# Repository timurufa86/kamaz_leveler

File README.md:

# Kamaz-Leveler

Прошивка системы выравнивания пневмоподвески (ESP32 + FreeRTOS + GitHub OTA).

- Базовая ветка разработки: **`2.x`** (старая линия; новая — `3.0.0`)
- Скетч старой линии: `kamaz_2_0_0_fr_adafruiti_OTA_NM/` (ESP32 classic, плата v2)
- Скетч новой линии: `kamaz_3_3_0_fr_adafruiti_OTA_NM/` (ESP32-S3, плата v3)
- Репозиторий: https://github.com/timurufa86/kamaz_leveler

## Аппаратная часть (PCB)

Проект платы (KiCad 10, 2 слоя, корпус 15-8) лежит в [`hardware/`](hardware/README.md).
Там же — документация, рендеры, производственные файлы и скрипты экспорта.

## Toolchain

- **arduino-cli** 1.5.1+
- Ядро: **esp32:esp32 3.3.11+**
- Библиотеки: из `C:\my\libraries` (подключаются через `arduino-cli.yaml`)

## Сборка

Библиотеки подключаются через проектный `arduino-cli.yaml`, где
`directories.user: C:/my` — то есть sketchbook указывает на `C:\my`, а
библиотеки берутся из `C:\my\libraries`.

```powershell
# Компиляция (экспортирует *.bin в build/esp32.esp32.esp32/)
./build.cmd

# Компиляция + прошивка на подключённую плату
./build.cmd COM5
```

Или напрямую:

```powershell
arduino-cli compile --config-file arduino-cli.yaml `
  -b "esp32:esp32:esp32:PartitionScheme=custom,FlashSize=4M" --warnings none --export-binaries `
  --build-property compiler.c.elf.extra_flags=-Wl,--allow-multiple-definition `
  kamaz_2_0_0_fr_adafruiti_OTA_NM
```

> `--warnings none` обязателен: библиотека GEM 1.8.1 содержит функцию без
> `return`, которую ядро ESP32 превращает в ошибку через `-Werror=return-type`.
> (Значение можно передавать как `-Wl,--allow-multiple-definition` или через
> `-D`, главное — попасть в `compiler.c.elf.extra_flags`.)

> `--build-property compiler.c.elf.extra_flags=-Wl,--allow-multiple-definition`
> обязателен, начиная с 8.6.0: библиотека GEM компилируется целиком (включая
> `GEM_u8g2.cpp`), из-за чего в сборку попадает библиотека `U8g2`, а её
> `src/clib/u8g2_fonts.c` дублирует символы шрифтов из
> `U8g2_for_Adafruit_GFX/src/u8g2_fonts.c`. Флаг разрешает дубликаты: линковщик
> оставляет первое определение, неиспользуемые секции удаляются `--gc-sections`.
> Без флага сборка падает на этапе линковки с `multiple definition of
> 'u8g2_font_...'`.

## Карта флеша (4 МБ, своя таблица разделов)

Плата оснащена **4 МБ** флеш-памяти. Штатные OTA-слоты ядра (1.25 МБ) малы
для скетча (~1.6 МБ), поэтому используется **своя схема разделов**
(`kamaz_2_0_0_fr_adafruiti_OTA_NM/partitions.csv`, `PartitionScheme=custom`):

| Раздел | Смещение | Размер | Назначение |
|---|---|---|---|
| `nvs` | 0x9000 | 20 КБ | Wi-Fi/настройки IDF |
| `otadata` | 0xe000 | 8 КБ | выбор OTA-слота |
| `app0` (ota_0) | 0x10000 | **1.75 МБ** | основной слот прошивки |
| `app1` (ota_1) | 0x1D0000 | **1.75 МБ** | слот для OTA-обновления |
| `spiffs` | 0x390000 | 384 КБ | LittleFS (`/config.txt`) |
| `coredump` | 0x3F0000 | 64 КБ | дамп при сбое |

Скетч ~1.6 МБ занимает ~87% слота; запас роста ~230 КБ на слот.

> ⚠️ **Смена карты флеша требует разовой прошивки по USB** (bootloader +
> partitions + app). OTA с прежней 16-мегабайтной схемы разделы НЕ переносит.

## Карта флеша (16 МБ, своя таблица разделов) — линия 3.0.0

Плата v3 (ESP32-S3) оснащена **16 МБ** флеш-памяти. Штатная схема
`PartitionScheme=default_8MB` содержит **один** слот приложения, поэтому OTA на
ней невозможен. Используется **своя схема разделов**
(`kamaz_3_3_0_fr_adafruiti_OTA_NM/partitions.csv`, `PartitionScheme=custom`):

| Раздел | Смещение | Размер | Назначение |
|---|---|---|---|
| `nvs` | 0x9000 | 20 КБ | Wi-Fi/настройки IDF |
| `otadata` | 0xe000 | 8 КБ | выбор OTA-слота |
| `app0` (ota_0) | 0x10000 | **2 МБ** | основной слот прошивки |
| `app1` (ota_1) | 0x210000 | **2 МБ** | слот для OTA-обновления |
| `spiffs` | 0x410000 | 11.9 МБ | LittleFS (`/config.txt`) |
| `coredump` | 0xFF0000 | 64 КБ | дамп при сбое |

Образ ~1.65 МБ, запас роста ~350 КБ на слот. Сборка:
`build_3_3_0.cmd` (FQBN `esp32:esp32:esp32s3:PartitionScheme=custom,FlashSize=16M,PSRAM=opi`).

> ⚠️ **Смена карты флеша требует разовой прошивки по USB** (bootloader +
> partitions + app). OTA с прежней `default_8MB` схемы разделы НЕ переносит.

## Две линии в одном репозитории (фильтр OTA по MAJOR)

Обе линии публикуют ассеты `kamaz_leveler.bin` / `kamaz_leveler.bin.sha256` в
одном репозитории, поэтому устройство фильтрует релизы по **MAJOR** из своего
`VERSION` (`ota_list.cpp`, `releaseMatchesLocalMajor`): релиз с другим MAJOR или
непарсящимся тегом пропускается с логом
`[OTA] skip release v3.0.0 (major 3 != 2)`. Устройство 2.0.0 никогда не
поставит образ 3.0.0 (ESP32-S3) и наоборот.

## Используемые библиотеки

Резолвятся из `C:\my\libraries`:

| Библиотека | Версия |
|---|---|
| ArduinoJson | 7.4.3 |
| Adafruit BusIO | 1.17.4 |
| Adafruit GFX Library | 1.12.6 |
| Adafruit ST7735 and ST7789 Library | 1.11.0 |
| Adafruit ADS1X15 | 2.6.2 |
| EncButton | 3.7.6 |
| GEM | 1.8.1 |
| GyverFilters | 3.3.0 |
| MPU6050 | 1.4.5 |
| U8g2_for_Adafruit_GFX | 1.8.0 |
| U8g2 (только как источник шрифтов, напрямую не подключается) | 2.36.19 |

## Настройки и сервис (8.8.0)

Новые параметры меню (все сохраняются в `/config.txt`, формат **3**, и подгружаются
при старте; старые `config.txt` форматов 1–2 читаются, новые поля = значения по умолчанию):

| Раздел меню | Пункты | Значение по умолчанию |
|---|---|---|
| Давление | Проверка МП,с | 240 |
| Клапаны | Макс.время,с; Зона нечувств.,бар | 10; 0.20 |
| Авторежим | Грубая зона; Точная зона; Порог «хуже» | 0.40; 0.15; 1.20 |
| Движение | Длительность,с; Успокоение,с; Проверка,с; Допуск,бар; Порог гиро; Порог аксель | 30/30/120/0.2/50/1000 |
| Дисплей | Гасить,мин (0 = никогда); Интервал,мс; Порог углов; Порог давл. | 0; 50; 0.05; 0.03 |
| IMU / MPU6050 | Порог детектора; Нуль X,град; Нуль Y,град | 100; 0.0; 0.0 |

Запись конфига — атомарная (`config.tmp` → `config.txt`, предыдущая версия в
`config.bak`), после записи файл проверяется чтением; при старте и после
сохранения в Serial печатается дамп всех значений (`[CFG] …`). Страница меню
**«Настройки»** показывает текущие значения на экране.

### Новые разделы меню

- **«IMU / MPU6050»**
  - **Обнулить углы** — текущее положение становится нулём (с подтверждением
    КН3/КН4); нуль сохраняется в конфиг и учитывается в показаниях и в авторежиме.
  - **Калибровка офсетов** — библиотечная `CalibrateGyro`/`CalibrateAccel` (DMP на
    время калибровки выключается), 6 офсетов сохраняются в конфиг и применяются при
    старте. Требуется ровная площадка и неподвижная машина 10–20 с.
  - **Диагностика MPU** — DeviceID, температура, углы, сырые `getMotion6`, офсеты,
    признак ошибки MPU.
  - **Порог детектора** — аппаратный `setMotionDetectionThreshold` (20…255).
- **Ручной тест клапанов** (раздел «Тестирование») — 6 выходов: ПЛ, ПП, ЗЛ, ЗП,
  НАКАЧКА, СБРОС. Кн1/Кн2 — выбор, **клапан открыт, пока удерживается КН3**,
  Кн4 — выход с закрытием всех клапанов; страховочный таймаут 15 с; доступно
  только в РУЧНОМ режиме без ошибок и вне OTA; аварийная остановка КН4+КН5
  также закрывает клапаны.
- **Гашение подсветки** — по бездействию N минут (`Дисплей → Гасить,мин`);
  первое нажатие только включает подсветку и не выполняет действие.

## Визуализация: экран ДВИЖЕНИЯ (8.9.0)

В режиме ДВИЖЕНИЯ главный экран автоматически сменяется отдельным «экраном движения»:

- цели передних/задних подушек (из настроек) vs текущие давления и рассогласование Δ
  с цветом по допуску (`Движение → Допуск,бар`);
- четыре карточки подушек: текущее значение, метка цели на полосе, Δ по каждой подушке;
- таймеры: «в движении N с», «СТАБИЛИЗАЦИЯ N с» (полоса), «след. проверка N с»,
  «последняя подкачка N с назад»;
- активные клапаны (накачка/сброс передних/задних) с анимацией «бегущих штрихов»;
- тренд (спарклайн) давлений за 30 с: две линии (перед/зад) + штриховые линии целей;
- режимные иконки из `icon.h` в статус-баре (20×20) и пульсирующий бейдж движения в шапке;
- сглаживание (интерполяция) значений и частичная перерисовка — без мерцания.

Логика движения и выравнивания не менялась — экран только читает данные. Наружу вынесены
две переменные времени последней корректировки (`movementLastAdjustFront/Rear`) и
добавлена отметка начала движения (`movementStartMs`).

## Меню и обновления (8.7.0)

- **Вход в меню** — удержание пары **КН3 + КН4** (GPIO15 + GPIO17, 2 с) из любого
  режима и экрана. **Аварийный стоп** — удержание пары **КН1 + КН4**
  (GPIO13 + GPIO17, 2 с); он обрабатывается первым и подавляет открытие меню.
- В меню: Кн1/Кн2 — навигация, Кн3 — ОК, Кн4 — назад (пункт «Назад» создаёт GEM для
  подстраниц), Кн5 — сохранить и выйти. Подсказка дублируется в шапке меню.
- Раздел **«Обновления»**: проверка GitHub, список до 3 релизов
  (`/releases?per_page=3`), карточка релиза (дата, размер, статус, SHA-256),
  установка последней или выбранной версии, режим ArduinoOTA (Wi-Fi).
- Экран прогресса обновления показывается в любом режиме, шапка «ОБНОВЛЕНИЕ»,
  крупный процент и предупреждение «Не выключайте питание».
- Wi-Fi: пароль единый (`asd12345`), экран выбора сети переведён на U8g2 (шкала
  уровня сигнала, усечение длинных имён).
- Страница «Информация» в меню — живая: версия, режим, MPU, давление в магистрали,
  Wi-Fi (SSID/RSSI), аптайм и свободная RAM, число активных ошибок.

## Home Assistant (10.16.0)

Интеграция по **HTTP REST**, включается в меню **Система → Дом (HA)**. Брокер не
нужен: устройство поднимает сервер на порту 80.

- `GET /api/state` — вся телеметрия; `GET /api/config` — все настройки;
  `POST /api/config` — безопасное подмножество; `POST /api/mode` — АВТО/РУЧНОЙ;
  `POST /api/manual` — start/stop/pulse; `POST /api/action` — reset/save/stop/restart.
- Необязательный токен `X-Api-Key` (Serial: `HA TOKEN <стр>`).
- Готовые файлы: `ha/kamaz_leveler_package.yaml`, `ha/kamaz_leveler_dashboard.yaml`,
  инструкция — `docs/HA_INTEGRATION.md`.
- На время OTA сервер останавливается (освобождает сокеты/кучу) и поднимается после.

## Версионирование и релиз

- SemVer: см. `.cursor/rules/semantic-versioning.mdc` (стиль папок/веток `9.0.0`).
- OTA-релиз: см. `.cursor/rules/github-ota-release.mdc`
  (ассеты `kamaz_leveler.bin` + `kamaz_leveler.bin.sha256`, тег `v9.0.0`).

## Типографика и визуализация (появились в 8.6.0)

Весь текст на экранах выводится через **U8g2_for_Adafruit_GFX** (UTF-8, честные
размеры шрифтов, кириллица) — слой из трёх модулей:

| Модуль | Назначение |
|---|---|
| `ui_theme.h` | палитра RGB565, сетка и метрики экрана (отступы, радиусы, высоты строк) |
| `ui_fonts.h` | шрифтовая лестница `UiFont` (Tiny…Huge) — кириллические шрифты U8g2 |
| `ui_text.h` / `.cpp` | класс `UiText` (экземпляр `ui`): печать по базовой линии, выравнивание и вертикальное центрирование в прямоугольнике, `printf`-варианты без динамической памяти, усечение строк с `..` |

Шрифтовая сетка (все с кириллицей):

| Роль | Шрифт | Применение |
|---|---|---|
| Tiny | `u8g2_font_5x7_t_cyrillic` | подсказки, подписи шкал |
| Small | `u8g2_font_6x13_t_cyrillic` | основной мелкий текст, списки |
| SmallB | `u8g2_font_6x13B_t_cyrillic` | акценты и подписи карточек |
| Body / BodyWide | `u8g2_font_7x13` / `8x13_t_cyrillic` | основной текст |
| Med | `u8g2_font_10x20_t_cyrillic` | заголовки экранов, значения |
| Large / XLarge / Huge | `u8g2_font_inr24/33/46_t_cyrillic` | крупные значения, сплэш |

Важно: `U8g2_for_Adafruit_GFX` **не масштабирует** текст (аналога `setTextSize`
нет), поэтому размер задаётся выбором шрифта — глифы остаются пиксель-в-пиксель
вместо растягивания. Меню GEM (`GEM_adafruit_gfx`) по-прежнему работает на
Adafruit-GFX-шрифтах `CourierCyr7`/`CourierCyr9` из `FontsRus/` — только для
пунктов меню; все остальные экраны переведены на U8g2.

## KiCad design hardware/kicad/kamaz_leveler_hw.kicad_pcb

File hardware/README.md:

# Kamaz Leveler — аппаратная часть (PCB)

Плата контроллера пневмоподвески Kamaz Leveler: **ESP32-C3**, 2 слоя, детали с двух сторон.
Проект KiCad 10.0.7. Механика согласована с корпусом **15-8** (чертёж `k_15-08-...pdf`).

## Текущий статус

| Параметр | Значение |
|---|---|
| Схема | `kicad/kamaz_leveler_hw.kicad_sch` — 113 компонентов (U7 = ESP32-C3-DevKitC-02) |
| Плата | `kicad/kamaz_leveler_hw.kicad_pcb` — 83 × 58 мм, 2 слоя, 117 футпринтов |
| Корпус | 4×Ø2,2 NPTH по контуру **28 × 61,6**; модуль сдвинут на −5 мм; J1/J2 — низ (окно 62×28), J3…J8 — верх (окно 42×20) |
| Разводка | **275 из 284 цепей (96,8%)**, 2394 трассы/вии |
| Электрика DRC | **0 замыканий, 0 нарушений зазора** (правило 0,127 мм) |
| Не разведено | 9 цепей: `/BUT1`, `/VIN_FUSED`, `/VLV_IN2,3,5`, `/ST_U3_34`, `/PRES_IN`, `/VLV_DRV1`, `/VLV_DRV4` |
| Прочие DRC | `copper_edge_clearance` 19, `track_width` 4, `via_dangling` 15, silk ~215, courtyard под модулем (намеренно) |
| Производство | `production/` — Gerber, Excellon, pos.csv, STEP, PDF, BOM (перегенерируется скриптом) |

> **Статус: не финальный релиз.** До производства осталось закрыть 9 цепей и почистить `copper_edge`/`via_dangling`.

## Структура

```
hardware/
├── README.md            ← этот файл
├── HANDOFF.md           ← журнал работ (история решений и бэкапов)
├── AGENT_HANDOFF.md     ← передача контекста следующему агенту (правила, грабли, план)
├── kicad/               ← сам проект KiCad
│   ├── kamaz_leveler_hw.kicad_pro / .sch / .pcb / .prl
│   ├── kamaz_leveler_hw.kicad_dru   ← кастомные правила DRC
│   ├── BOM.csv
│   ├── fp-lib-table, sym-lib-table  ← локальные библиотеки (${KIPRJMOD})
│   ├── kamaz.pretty/, kamaz_leveler_hw.pretty/
│   ├── kamaz_leveler.kicad_sym
│   └── 3dmodels/        ← STEP-модели компонентов
├── docs/                ← HARDWARE.md, CALCULATIONS.md, ТЗ, таблица расстановки
├── images/              ← актуальные рендеры платы и схемы
├── production/          ← выходные файлы для завода (Gerber/сверловка/pos/STEP/PDF/BOM)
├── scripts/             ← экспорт и рендер (см. ниже)
├── 3d/                  ← сборка платы в STEP
└── backups/             ← ключевые бэкапы платы (даты в имени)
```

## Как открыть

1. KiCad 10.0.7 → **File → Open Project** → `kicad/kamaz_leveler_hw.kicad_pro`.
2. Библиотеки подключаются автоматически: `${KIPRJMOD}` указывает на `kicad/`, таблицы `fp-lib-table`/`sym-lib-table` уже в проекте.
3. DRC: `Inspect → Design Rules Checker` (правила — `kamaz_leveler_hw.kicad_dru`).

## Как перегенерировать производство

```bash
"C:\Program Files\KiCad\10.0\bin\python.exe" scripts\export_prod.py
```

Скрипт кладёт в `production/`: Gerber (2 слоя, без Protel-расширений), Excellon + карты сверловки, `pos.csv`, `board.step`, `board.pdf`, `board_stats.txt`, `schematic.pdf`, `BOM.csv`.

## Зависимости

| Что | Где |
|---|---|
| KiCad 10.0.7 (`kicad-cli`, `pcbnew` Python) | `C:\Program Files\KiCad\10.0\` |
| Python с `pcbnew` | `C:\Program Files\KiCad\10.0\bin\python.exe` |
| FreeRouting 2.5.0 + JRE 25 | `C:\my\freerouting\` |
| PIL (для рендеров) | системный Python |

## Известные ограничения / waivers

- **Courtyard под модулем ESP32** — детали на обратной стороне под модулем (высота ≤5 мм) стоят намеренно; DRC это помечает.
- **Silk** — пересечения шелкографии с падами/друг другом: косметика, на электрику не влияет.
- **9 несоединённых цепей** — список выше; для 2 слоёв это остаток после автотрассировки, требует ручной доработки.

## История

- 2026-11-01: перепроектирование под корпус 15-8, новая расстановка (SA по HPWL с весами «трудных» цепей), 275/284.
- 2026-11-04: проект перенесён в этот репозиторий (`hardware/`), структура упорядочена, производство перегенерировано.

Подробный журнал — `HANDOFF.md`.

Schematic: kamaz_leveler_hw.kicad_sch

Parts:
C1, C3, C10, C16, C17, C20, C22, C23, C24, C25, C26, C27, C29, C31, C32, C33, C35: 100nF; C_0805_2012Metric
C2: 470uF; CP_Elec_8x10
C4, C5, C7, C11, C12, C14, C15, C21, C30: 10uF; C_1206_3216Metric
C6: 100uF; CP_EIA-7132-20_AVX-U
C8: 4.7nF; C_0805_2012Metric
C9: 47pF; C_0805_2012Metric
C13: 100uF; CP_EIA-6032-15_Kemet-U_Pad2.25x2.35mm_HandSolder
C18: 10uF; CP_EIA-3528-12_Kemet-T_HandSolder
C19: 10uF; C_0805_2012Metric
C28: 330uF/35V; CP_Elec_8x10
D1: 1.5KE36CA; D_DO-201AD_P15.24mm_Horizontal_Pad2.0_Drill1.3
D2: SS54; D_SMC
D3: SS34; D_SMC
D4, D11, D12, D13, D14, D15, D16: LED; LED_0805_2012Metric
D5, D6, D7, D8, D9, D10: SS34; D_SMA
D17, D18: BZX84C3V3; SOT-23
D20: SMAJ12A; D_SMA
F1: 5A; Fuseholder_Blade_Mini_Keystone_3568
H1, H2, H3, H4: MountingHole_3.2mm_M3_Pad6
J1, J8: Conn_01x02_Pin; PinHeader_1x02_P2.54mm_Vertical
J2: Conn_01x07_Pin; PinHeader_1x07_P2.54mm_Vertical
J3: Conn_01x06_Pin; PinHeader_1x06_P2.54mm_Vertical
J4, J6, J7: Conn_01x04_Pin; PinHeader_1x04_P2.54mm_Vertical
J5: Conn_01x08_Pin; PinHeader_1x08_P2.54mm_Vertical
JP1: Jumper; SolderJumper-2_P1.3mm_Open_RoundedPad1.0x1.5mm
L2: 33uH; L_Bourns_SRP1245A
L3: 10uH; L_Bourns-SRN1060
L4: 10uH; L_Bourns_SRP1245A
Q1: IRF9540N; TO-220-3_Vertical
R1, R4, R9, R11, R12, R13, R14, R15, R16, R18, R19, R29, R30, R31, R32, R33, R34, R35, R36, R37, R38, R39, R42, R43: 10k; R_0805_2012Metric
R2: 47k; R_0805_2012Metric
R3, R41: 100k; R_0805_2012Metric
R5: 6.49k; R_0805_2012Metric
R6: 91k; R_0805_2012Metric
R10: 52.3k; R_0805_2012Metric
R20, R21, R23, R24, R25, R26, R27, R28: 4.7k; R_0805_2012Metric
R22: 1k; R_0805_2012Metric
R40: 20k; R_0805_2012Metric
U1: TPS54560BDDA; SOIC-8-1EP_3.9x4.9mm_P1.27mm_EP2.95x4.9mm_Mask2.71x3.4mm_Th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
U2: AP3211K; SOT-23-6
U3, U4: BTS724G; Infineon_SOIC-20W_7.6x12.8mm_P1.27mm
U5: 74HCT541; SOIC-20W_7.5x12.8mm_P1.27mm
U6: PCAL9555APW; TSSOP-24_4.4x7.8mm_P0.65mm
U7: ESP32-DevKitC_30P; ESP32-C3-DevKitC-02
U8: AMS1117-3.3; SOT-223-3_TabPin2
U11: 78L08; SOT-89-3
U12: 74LVC1G14; SOT-23-5

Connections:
+3V3: C15.1, C17.1, C18.1, C21.1, C22.1, C29.1, C35.1, J4.1, J5.2, J6.1, R18.1, R19.1, R20.1, R21.1, R29.1, R30.1, R31.1, R32.1, R33.1, R34.1, R35.1, R36.1, R37.1, R38.1, R41.1, R43.2, U6.24 (VDD), U8.2 (VO), U12.5 (VCC)
+3V3_ESP: U7.30 (3V3)
+5V: C13.1, C14.1, C16.1, C19.1, C20.1, L3.2, R10.1, R22.1, U5.20 (VCC), U7.15 (VIN), U8.3 (VI)
+12V: C6.1, C7.1, C11.1, C12.1, C30.1, D5.1 (K), D6.1 (K), D7.1 (K), D8.1 (K), D9.1 (K), D10.1 (K), L2.2, R6.1, U2.4 (EN), U2.5 (IN), U3.1 (VBB), U3.10 (VBB), U3.11 (VBB), U3.12 (VBB), U3.15 (VBB), U3.16 (VBB), U3.19 (VBB), U3.20 (VBB), U4.1 (VBB), U4.10 (VBB), U4.11 (VBB), U4.12 (VBB), U4.15 (VBB), U4.16 (VBB), U4.19 (VBB), U4.20 (VBB), U11.3 (IN)
+24V: C1.1, C2.1, C4.1, C5.1, C28.1, D1.1 (A1), Q1.3 (S), R2.1, U1.2 (VIN), U1.3 (EN)
/+8V_SENS: C31.1, J7.1, JP1.1 (A), U11.1 (OUT)
/+24V_IN: F1.1, J1.1
/BOOT1: C3.1, U1.1 (BOOT)
/BOOT2: C10.1, U2.1 (BS)
/BUT1: C23.1, J3.2, R29.2, U6.15 (IO1_2)
/BUT2: C24.1, J3.3, R30.2, U6.16 (IO1_3)
/BUT3: C25.1, J3.4, R31.2, U6.17 (IO1_4)
/BUT4: C26.1, J3.5, R32.2, U6.18 (IO1_5)
/BUT5: C27.1, J3.6, R19.2, U6.19 (IO1_6)
/COMP1: C9.2, R4.1, U1.6 (COMP)
/COMP1_R: C8.1, R4.2
/DISP_BL: J5.8, U7.26 (IO4)
/DISP_CS: J5.7, R18.2, U7.23 (IO5)
/DISP_DC: J5.6, U7.25 (IO16)
/DISP_MOSI: J5.4, U7.16 (IO23)
/DISP_RES: J5.5, U7.21 (IO19)
/DISP_SCLK: J5.3, U7.22 (IO18)
/EXT_8V: J7.4, JP1.2 (B)
/FB1: C9.1, R5.1, R6.2, U1.5 (FB)
/FB2: R9.1, R10.2, U2.3 (FB)
/I2C_SCL: J4.3, J6.3, R21.2, U6.22 (SCL), U7.17 (IO22)
/I2C_SDA: J4.2, J6.2, R20.2, U6.23 (SDA), U7.20 (IO21)
/INT_MCU: R37.2, U6.1 (~INT), U7.7 (IO33)
/LED_A: D4.2 (A), R22.2
/PRES_IN: J8.1, R42.1
/PRES_SW: C33.1, D18.1 (K), R41.2, R42.2, U7.8 (IO25)
/Q1_GATE: Q1.1 (G), R1.1, R2.2
/RT1: R3.1, U1.4 (RT/CLK)
/SPEED_PULSE: U7.5 (IO35), U12.4
/SPEED_SIG: D20.1 (A1), J7.3, R39.1
/SP_DIV: C32.1, D17.1 (K), R39.2, R40.1, U12.2
/ST_U3_12: R33.2, U3.4 (ST1/2), U6.10 (IO0_6)
/ST_U3_34: R34.2, U3.8 (ST3/4), U6.11 (IO0_7)
/ST_U4_12: R35.2, U4.4 (ST1/2), U6.13 (IO1_0)
/ST_U4_34: R36.2, U4.8 (ST3/4), U6.14 (IO1_1)
/SW1: C3.2, D2.1 (K), L2.1, U1.8 (SW)
/SW2: C10.2, D3.1 (K), L3.1, U2.6 (SW)
/VALVE_BUB1: D5.2 (A), D11.2 (A), J2.2, U3.18 (OUT1)
/VALVE_BUB2: D6.2 (A), D12.2 (A), J2.3, U3.17 (OUT2)
/VALVE_BUB3: D7.2 (A), D13.2 (A), J2.4, U3.14 (OUT3)
/VALVE_BUB4: D8.2 (A), D14.2 (A), J2.5, U3.13 (OUT4)
/VALVE_DEFL: D10.2 (A), D16.2 (A), J2.7, U4.17 (OUT2)
/VALVE_INFL: D9.2 (A), D15.2 (A), J2.6, U4.18 (OUT1)
/VIN_FILT: L4.2, Q1.2 (D)
/VIN_FUSED: F1.2, L4.1
/VLV_DRV1: R11.1, U3.3 (IN1), U5.18 (Y0)
/VLV_DRV2: R12.1, U3.5 (IN2), U5.17 (Y1)
/VLV_DRV3: R13.1, U3.7 (IN3), U5.16 (Y2)
/VLV_DRV4: R14.1, U3.9 (IN4), U5.15 (Y3)
/VLV_DRV5: R15.1, U4.3 (IN1), U5.14 (Y4)
/VLV_DRV6: R16.1, U4.5 (IN2), U5.13 (Y5)
/VLV_EN: R38.2, U5.1 (G1), U5.19 (G2), U7.6 (IO32)
/VLV_IN1: U5.2 (A0), U6.4 (IO0_0)
/VLV_IN2: U5.3 (A1), U6.5 (IO0_1)
/VLV_IN3: U5.4 (A2), U6.6 (IO0_2)
/VLV_IN4: U5.5 (A3), U6.7 (IO0_3)
/VLV_IN5: U5.6 (A4), U6.8 (IO0_4)
/VLV_IN6: U5.7 (A5), U6.9 (IO0_5)
/VLV_LED1: D11.1 (K), R23.1
/VLV_LED2: D12.1 (K), R24.1
/VLV_LED3: D13.1 (K), R25.1
/VLV_LED4: D14.1 (K), R26.1
/VLV_LED5: D15.1 (K), R27.1
/VLV_LED6: D16.1 (K), R28.1
GND: C1.2, C2.2, C4.2, C5.2, C6.2, C7.2, C8.2, C11.2, C12.2, C13.2, C14.2, C15.2, C16.2, C17.2, C18.2, C19.2, C20.2, C21.2, C22.2, C23.2, C24.2, C25.2, C26.2, C27.2, C28.2, C29.2, C30.2, C31.2, C32.2, C33.2, C35.2, D1.2 (A2), D2.2 (A), D3.2 (A), D4.1 (K), D17.2 (A), D18.2 (A), D20.2 (A2), J1.2, J2.1, J3.1, J4.4, J5.1, J6.4, J7.2, J8.2, R1.2, R3.2, R5.2, R9.2, R11.2, R12.2, R13.2, R14.2, R15.2, R16.2, R23.2, R24.2, R25.2, R26.2, R27.2, R28.2, R40.2, U1.7 (GND), U1.9 (GND), U2.2 (GND), U3.2 (GND1/2), U3.6 (GND3/4), U4.2 (GND1/2), U4.6 (GND3/4), U4.7 (IN3), U4.9 (IN4), U5.8 (A6), U5.9 (A7), U5.10 (GND), U6.2 (A1), U6.3 (A2), U6.12 (VSS), U6.21 (A0), U7.14 (GND), U7.29 (GND), U8.1 (GND), U11.2 (GND), U12.3 (GND)
unnamed: R43.1, U7.1 (EN)

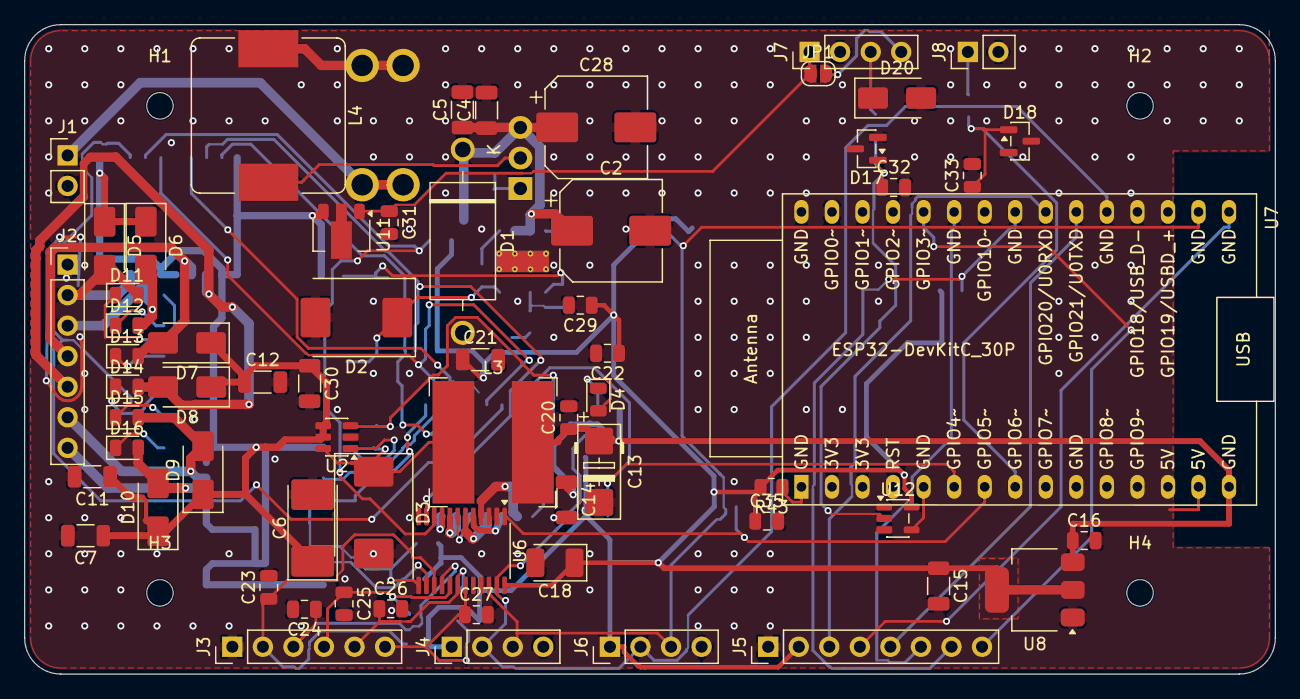
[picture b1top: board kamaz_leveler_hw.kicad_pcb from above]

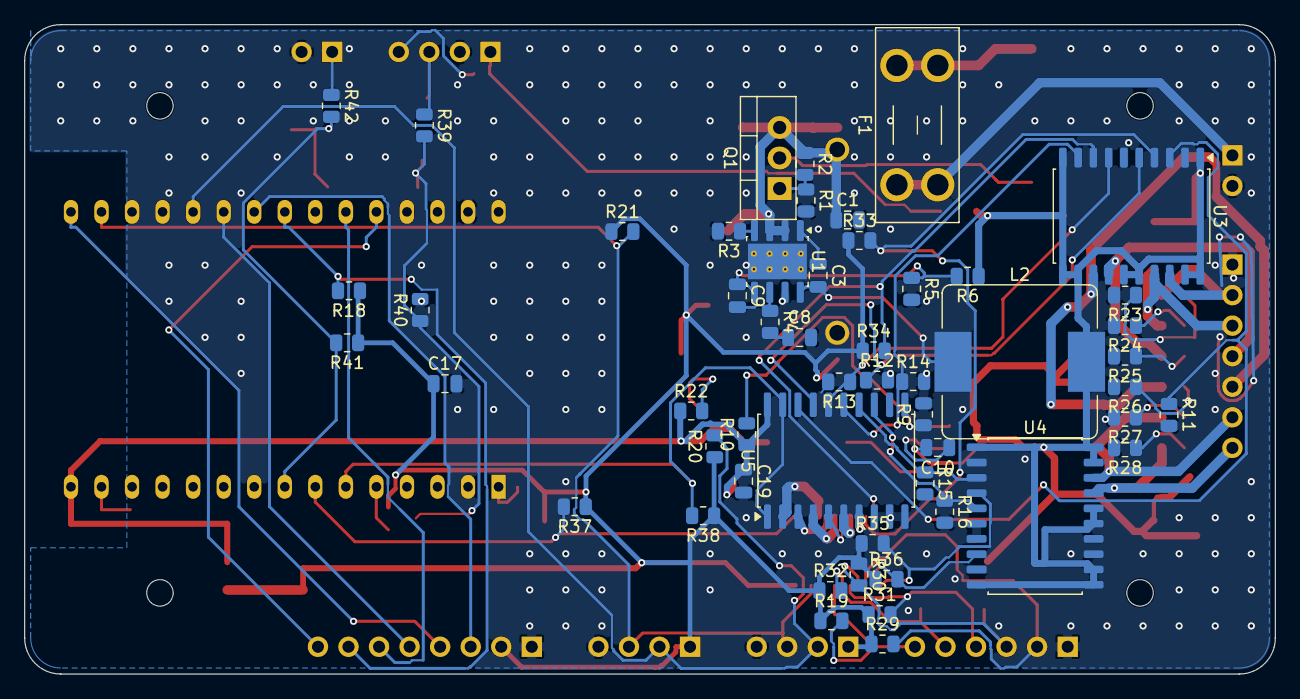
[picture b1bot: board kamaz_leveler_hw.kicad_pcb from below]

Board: 2 copper layers, 104.0 x 54.0 mm, 121 parts (53 on the bottom side), 70 nets.

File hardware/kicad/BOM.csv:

"Reference","Value","Footprint","Description"
"C1,C3,C10,C16,C17,C20,C22-C27,C29,C31-C33,C35","100nF","Capacitor_SMD:C_0805_2012Metric","Unpolarized capacitor"
"C2","470uF","Capacitor_SMD:CP_Elec_8x10","Polarized capacitor"
"C4,C5,C7,C11,C12,C14,C15,C21,C30","10uF","Capacitor_SMD:C_1206_3216Metric","Unpolarized capacitor"
"C6","100uF","Capacitor_Tantalum_SMD:CP_EIA-7132-20_AVX-U","Polarized capacitor"
"C8","4.7nF","Capacitor_SMD:C_0805_2012Metric","Unpolarized capacitor"
"C9","47pF","Capacitor_SMD:C_0805_2012Metric","Unpolarized capacitor"
"C13","100uF","PCM_Capacitor_Tantalum_SMD_AKL:CP_EIA-6032-15_Kemet-U_Pad2.25x2.35mm_HandSolder","Polarized capacitor"
"C18","10uF","Capacitor_Tantalum_SMD:CP_EIA-3528-12_Kemet-T_HandSolder","Polarized capacitor"
"C19","10uF","Capacitor_SMD:C_0805_2012Metric","Unpolarized capacitor"
"C28","330uF/35V","Capacitor_SMD:CP_Elec_8x10","Polarized capacitor"
"D1","1.5KE36CA","kamaz_leveler:D_DO-201AD_P15.24mm_Horizontal_Pad2.0_Drill1.3","1500W bidirectional TVS diode, DO-201AE"
"D2","SS54","Diode_SMD:D_SMC","Schottky diode"
"D3","SS34","Diode_SMD:D_SMC","Schottky diode"
"D4,D11-D16","LED","LED_SMD:LED_0805_2012Metric","Light emitting diode"
"D5-D10","SS34","Diode_SMD:D_SMA","40V 3A Schottky Diode, SMA"
"D17,D18","BZX84C3V3","Package_TO_SOT_SMD:SOT-23","Zener diode"
"D20","SMAJ12A","Diode_SMD:D_SMA","400W unidirectional Transient Voltage Suppressor, 12.0Vr, SMA(DO-214AC)"
"F1","5A","Fuse:Fuseholder_Blade_Mini_Keystone_3568","Fuse"
"J1,J8","Conn_01x02_Pin","Connector_PinHeader_2.54mm:PinHeader_1x02_P2.54mm_Vertical","Generic connector, single row, 01x02, script generated"
"J2","Conn_01x07_Pin","Connector_PinHeader_2.54mm:PinHeader_1x07_P2.54mm_Vertical","Generic connector, single row, 01x07, script generated"
"J3","Conn_01x06_Pin","Connector_PinHeader_2.54mm:PinHeader_1x06_P2.54mm_Vertical","Generic connector, single row, 01x06, script generated"
"J4,J6,J7","Conn_01x04_Pin","Connector_PinHeader_2.54mm:PinHeader_1x04_P2.54mm_Vertical","Generic connector, single row, 01x04, script generated"
"J5","Conn_01x08_Pin","Connector_PinHeader_2.54mm:PinHeader_1x08_P2.54mm_Vertical","Generic connector, single row, 01x08, script generated"
"JP1","Jumper","Jumper:SolderJumper-2_P1.3mm_Open_RoundedPad1.0x1.5mm","Solder Jumper, 2-pole, open"
"L2","33uH","Inductor_SMD:L_Bourns_SRP1245A","Inductor"
"L3","10uH","Inductor_SMD:L_Bourns-SRN1060","Inductor"
"L4","10uH","Inductor_SMD:L_Bourns_SRP1245A","Inductor"
"Q1","IRF9540N","Package_TO_SOT_THT:TO-220-3_Vertical","-23A Id, -100V Vds, 117mOhm Rds, P-Channel HEXFET Power MOSFET, TO-220"
"R1,R4,R9,R11-R16,R18,R19,R29-R39,R42,R43","10k","Resistor_SMD:R_0805_2012Metric","Resistor"
"R2","47k","Resistor_SMD:R_0805_2012Metric","Resistor"
"R3,R41","100k","Resistor_SMD:R_0805_2012Metric","Resistor"
"R5","6.49k","Resistor_SMD:R_0805_2012Metric","Resistor"
"R6","91k","Resistor_SMD:R_0805_2012Metric","Resistor"
"R10","52.3k","Resistor_SMD:R_0805_2012Metric","Resistor"
"R20,R21,R23-R28","4.7k","Resistor_SMD:R_0805_2012Metric","Resistor"
"R22","1k","Resistor_SMD:R_0805_2012Metric","Resistor"
"R40","20k","Resistor_SMD:R_0805_2012Metric","Resistor"
"U1","TPS54560BDDA","Package_SO:SOIC-8-1EP_3.9x4.9mm_P1.27mm_EP2.95x4.9mm_Mask2.71x3.4mm_ThermalVias","5A, Step Down DC-DC Converter, 4.5-60V Input Voltage, Texas R-PDSO-G8"
"U2","AP3211K","Package_TO_SOT_SMD:SOT-23-6","1.5A, Adjustable Step-Down Voltage Regulator, 1.4MHz Frequency, Vin=4.5..18V, Vout=0.81..15V, SOT-23-6"
"U3,U4","BTS724G","Package_SO:Infineon_SOIC-20W_7.6x12.8mm_P1.27mm","Smart High-Side Power Switch, PROFET, 4 Channel, RON 90mOhm, IL(NOM) 3.3A, Vbb 5.5...40V, standby current 9 µA (Tj = -40...25°C), SOIC-20"
"U5","74HCT541","Package_SO:SOIC-20W_7.5x12.8mm_P1.27mm","8-bit Buffer/Line Driver 3-state outputs"
"U6","PCAL9555APW","Package_SO:TSSOP-24_4.4x7.8mm_P0.65mm","IO expander 16 GPIO, I2C 400kHz, Interrupt, 2.3 - 5.5V, TSSOP-24"
"U7","ESP32-DevKitC_30P","PCM_Espressif:ESP32-C3-DevKitC-02",""
"U8","AMS1117-3.3","Package_TO_SOT_SMD:SOT-223-3_TabPin2","1A Low Dropout regulator, positive, 3.3V fixed output, SOT-223"
"U11","78L08","Package_TO_SOT_SMD:SOT-89-3","Positive 100mA 30V Linear Regulator, Fixed Output 8V, SOT-89"
"U12","74LVC1G14","Package_TO_SOT_SMD:SOT-23-5","Single Schmitt NOT Gate, Low-Voltage CMOS"

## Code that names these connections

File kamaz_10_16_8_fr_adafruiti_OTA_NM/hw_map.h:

#pragma once
/**
 * hw_map.h — карта железа платы v2 (Kamaz-Leveler).
 *
 * Плата v2: ESP32 DevKitC + PCAL9555APW (I2C 0x20) + U5 74HCT541 (буфер, OE = VLV_EN)
 *           + 2 x BTS724G (high-side клапаны) + J7 (датчик скорости) + J8 (аварийное давление).
 *
 * ПРАВИЛА:
 *  1) VLV_EN = HIGH  → буфер U5 в Hi-Z → входы BTS прижаты к GND → ВСЕ клапаны закрыты (fail-safe).
 *     VLV_EN = LOW   → буфер активен, клапаны управляются битами PCAL P00..P05.
 *  2) Клапаны и кнопки НЕ управляются GPIO ESP32 напрямую — только через PCAL9555APW.
 *  3) ST-выводы BTS724G — open-drain, активный низкий: 0 = неисправность пары каналов.
 *  4) Кнопки активны низким уровнем (нажата = 0), на плате внешние подтяжки 10 к.
 */

#include <Arduino.h>
#include "app_types.h"   // Pad, PAD_COUNT

/* ======================= ESP32 GPIO (плата v2) ======================= */

/** U5 OE (буфер клапанов). HIGH = Hi-Z = клапаны закрыты (fail-safe). */
constexpr uint8_t PIN_VLV_EN   = 32;

/** PCAL9555APW INT (open-drain, активный низкий). */
constexpr uint8_t PIN_PCAL_INT = 33;

/** Импульсный вход датчика скорости (input-only, PCNT). */
constexpr uint8_t PIN_SPEED_IN = 35;

/** Дискретный датчик аварийно низкого давления в рессивере (активный низкий). */
constexpr uint8_t PIN_PRES_SW  = 25;

/* ======================= PCAL9555APW ======================= */

constexpr uint8_t PCAL_I2C_ADDR = 0x20;   // A0..A2 = GND

/* Регистры PCAL9555A (базовые, совместимы с PCA9555) */
constexpr uint8_t PCAL_REG_INPUT0     = 0x00;
constexpr uint8_t PCAL_REG_INPUT1     = 0x01;
constexpr uint8_t PCAL_REG_OUTPUT0    = 0x02;
constexpr uint8_t PCAL_REG_OUTPUT1    = 0x03;
constexpr uint8_t PCAL_REG_POLARITY0  = 0x04;
constexpr uint8_t PCAL_REG_POLARITY1  = 0x05;
constexpr uint8_t PCAL_REG_CONFIG0    = 0x06;   // 1 = вход, 0 = выход
constexpr uint8_t PCAL_REG_CONFIG1    = 0x07;

/* Agile I/O (PCAL9555A). На TCA9535PWR этих регистров нет — писать «best effort». */
constexpr uint8_t PCAL_REG_DRIVE0     = 0x40;   // drive strength port 0
constexpr uint8_t PCAL_REG_DRIVE1     = 0x41;
constexpr uint8_t PCAL_REG_LATCH0     = 0x44;
constexpr uint8_t PCAL_REG_LATCH1     = 0x45;
constexpr uint8_t PCAL_REG_INTMASK0   = 0x4A;
constexpr uint8_t PCAL_REG_INTMASK1   = 0x4B;

/* --- Номера бит PCAL (P00..P17) --- */
constexpr uint8_t PCAL_P00 = 0;   // VLV_IN1 -> U5.A0 -> BTS U3.IN1 -> клапан ПЛ (BUB1)
constexpr uint8_t PCAL_P01 = 1;   // VLV_IN2 -> ... ПП (BUB2)
constexpr uint8_t PCAL_P02 = 2;   // VLV_IN3 -> ... ЗЛ (BUB3)
constexpr uint8_t PCAL_P03 = 3;   // VLV_IN4 -> ... ЗП (BUB4)
constexpr uint8_t PCAL_P04 = 4;   // VLV_IN5 -> INFL (общий впуск)
constexpr uint8_t PCAL_P05 = 5;   // VLV_IN6 -> DEFL (общий выпуск)
constexpr uint8_t PCAL_P06 = 6;   // ST_U3_12  (open-drain, 0 = fault)
constexpr uint8_t PCAL_P07 = 7;   // ST_U3_34
constexpr uint8_t PCAL_P10 = 8;   // ST_U4_12
constexpr uint8_t PCAL_P11 = 9;   // ST_U4_34 (неиспользуемые каналы U4)
constexpr uint8_t PCAL_P12 = 10;  // BUT1 / KN1
constexpr uint8_t PCAL_P13 = 11;  // BUT2 / KN2
constexpr uint8_t PCAL_P14 = 12;  // BUT3 / KN3
constexpr uint8_t PCAL_P15 = 13;  // BUT4 / KN4
constexpr uint8_t PCAL_P16 = 14;  // BUT5 / KN5
constexpr uint8_t PCAL_P17 = 15;  // резерв (не использовать)

/* --- Маски клапанов --- */
constexpr uint16_t PCAL_VLV_PAD0  = (uint16_t)(1u << PCAL_P00);
constexpr uint16_t PCAL_VLV_PAD1  = (uint16_t)(1u << PCAL_P01);
constexpr uint16_t PCAL_VLV_PAD2  = (uint16_t)(1u << PCAL_P02);
constexpr uint16_t PCAL_VLV_PAD3  = (uint16_t)(1u << PCAL_P03);
constexpr uint16_t PCAL_VLV_PADS  = (uint16_t)(PCAL_VLV_PAD0 | PCAL_VLV_PAD1 |
                                               PCAL_VLV_PAD2 | PCAL_VLV_PAD3);
constexpr uint16_t PCAL_VLV_INFL  = (uint16_t)(1u << PCAL_P04);
constexpr uint16_t PCAL_VLV_DEFL  = (uint16_t)(1u << PCAL_P05);
constexpr uint16_t PCAL_VLV_ALL   = (uint16_t)(PCAL_VLV_PADS | PCAL_VLV_INFL | PCAL_VLV_DEFL);

/* --- Маски ST-флагов (активный низкий) --- */
constexpr uint16_t PCAL_ST_U3_12  = (uint16_t)(1u << PCAL_P06);
constexpr uint16_t PCAL_ST_U3_34  = (uint16_t)(1u << PCAL_P07);
constexpr uint16_t PCAL_ST_U4_12  = (uint16_t)(1u << PCAL_P10);
constexpr uint16_t PCAL_ST_U4_34  = (uint16_t)(1u << PCAL_P11);
constexpr uint16_t PCAL_ST_ALL    = (uint16_t)(PCAL_ST_U3_12 | PCAL_ST_U3_34 |
                                               PCAL_ST_U4_12 | PCAL_ST_U4_34);

/* --- Маски кнопок (активный низкий) --- */
constexpr uint16_t PCAL_BTN_KN1 = (uint16_t)(1u << PCAL_P12);
constexpr uint16_t PCAL_BTN_KN2 = (uint16_t)(1u << PCAL_P13);
constexpr uint16_t PCAL_BTN_KN3 = (uint16_t)(1u << PCAL_P14);
constexpr uint16_t PCAL_BTN_KN4 = (uint16_t)(1u << PCAL_P15);
constexpr uint16_t PCAL_BTN_KN5 = (uint16_t)(1u << PCAL_P16);
constexpr uint16_t PCAL_BTN_ALL = (uint16_t)(PCAL_BTN_KN1 | PCAL_BTN_KN2 | PCAL_BTN_KN3 |
                                             PCAL_BTN_KN4 | PCAL_BTN_KN5);

/* --- Направления (config-регистр: 1 = вход) --- */
constexpr uint16_t PCAL_OUTPUT_MASK = PCAL_VLV_ALL;                       // P00..P05 — выходы
constexpr uint16_t PCAL_DIR_VALUE   = (uint16_t)(~PCAL_OUTPUT_MASK);      // остальное — входы

/* --- Адресация «подушка → бит» --- */
constexpr uint16_t pcalPadMask(Pad pad) {
  return (uint16_t)(1u << (uint8_t)pad);   // Pad 0..3 -> P00..P03
}

/* --- Виртуальные пины кнопок (ID для EncButton; НЕ GPIO) --- */
constexpr uint8_t BTN_VPIN_KN1 = 13;
constexpr uint8_t BTN_VPIN_KN2 = 12;
constexpr uint8_t BTN_VPIN_KN3 = 15;
constexpr uint8_t BTN_VPIN_KN4 = 17;
constexpr uint8_t BTN_VPIN_KN5 = 34;

/* ======================= ST-диагностика ======================= */

struct StGroup {
  uint16_t    stMask;    // бит ST в PCAL
  uint16_t    chanMask;  // биты клапанов, входящих в группу
  const char *name;      // для лога/UI
};

constexpr StGroup ST_GROUPS[] = {
    { PCAL_ST_U3_12, (uint16_t)(PCAL_VLV_PAD0 | PCAL_VLV_PAD1), "BUB1/BUB2" },
    { PCAL_ST_U3_34, (uint16_t)(PCAL_VLV_PAD2 | PCAL_VLV_PAD3), "BUB3/BUB4" },
    { PCAL_ST_U4_12, (uint16_t)(PCAL_VLV_INFL | PCAL_VLV_DEFL), "INFL/DEFL" },
};
constexpr uint8_t ST_GROUP_COUNT = (uint8_t)(sizeof(ST_GROUPS) / sizeof(ST_GROUPS[0]));

/* ======================= Тайминги/константы ======================= */

constexpr uint32_t PCAL_I2C_TIMEOUT_MS   = 3;      // на одну транзакцию
constexpr uint8_t  PCAL_I2C_RETRIES      = 3;      // попыток на операцию
constexpr uint32_t PCAL_REINIT_PERIOD_MS = 1000;   // backoff при отсутствии/сбое
constexpr uint32_t ST_POLL_MS            = 20;     // опрос ST/кнопок
constexpr uint32_t ST_BLOCK_MS           = 5000;   // пауза между попытками идентификации канала
constexpr uint32_t ST_PROBE_MS           = 30;     // включение канала при идентификации
constexpr uint32_t PRES_SW_DEBOUNCE_MS   = 50;
constexpr uint32_t PRES_SW_MISMATCH_MS   = 2000;   // расхождение с JHM1200
constexpr float    PRES_LOW_BAR_DEFAULT  = 4.9f;   // 5 ± 0,5 кгс/см²
constexpr uint32_t SPEED_WINDOW_MS       = 500;
constexpr uint32_t SPEED_TIMEOUT_MS      = 1000;
constexpr float    SPEED_MIN_VALID_KPH   = 0.5f;
constexpr float    SPEED_MAX_KPH         = 200.0f;
constexpr float    SPEED_EMA_ALPHA       = 0.3f;
constexpr uint32_t ODO_SAVE_PERIOD_MS    = 60000;

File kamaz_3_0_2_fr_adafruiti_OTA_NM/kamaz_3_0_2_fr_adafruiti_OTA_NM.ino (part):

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  // 3.0.0: клапаны на ESP32-S3 не имеют GPIO — ими управляет PCAL9555A (I2C).
  // Первым делом /VLV_EN = HIGH: буфер U5 в Hi-Z, все клапаны закрыты аппаратно,
  // ещё до Wire.begin/PCAL. Инициализация PCAL — после подъёма шины (см. шаг 4).
  pinMode(PIN_VLV_EN, OUTPUT);
  digitalWrite(PIN_VLV_EN, HIGH);
  pinMode(PIN_PCAL_INT, INPUT_PULLUP);
  closeAllValves();

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
  // ========== 4. WIRE ==========
  /* 3.0.0: I2C платы v3 — SDA=IO21, SCL=IO47 (ESP32-S3 не имеет GPIO22). */
  Wire.begin(PIN_I2C_SDA, PIN_I2C_SCL);
  Wire.setClock(100000L);  // старт на 100 кГц — надёжнее для MPU; после DMP поднимем до 400
  delay(50);

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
